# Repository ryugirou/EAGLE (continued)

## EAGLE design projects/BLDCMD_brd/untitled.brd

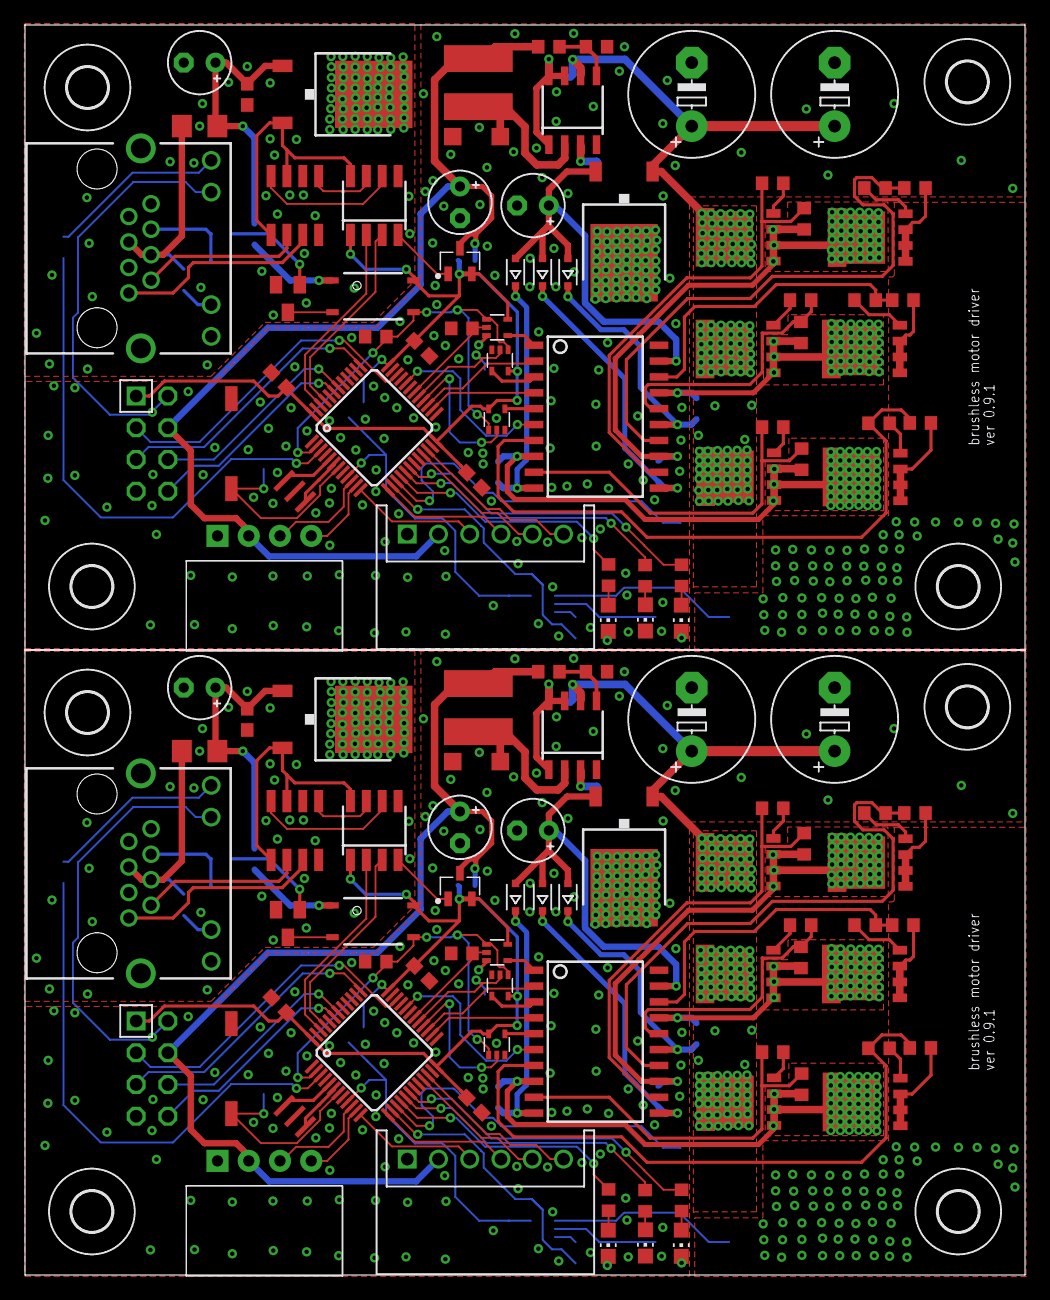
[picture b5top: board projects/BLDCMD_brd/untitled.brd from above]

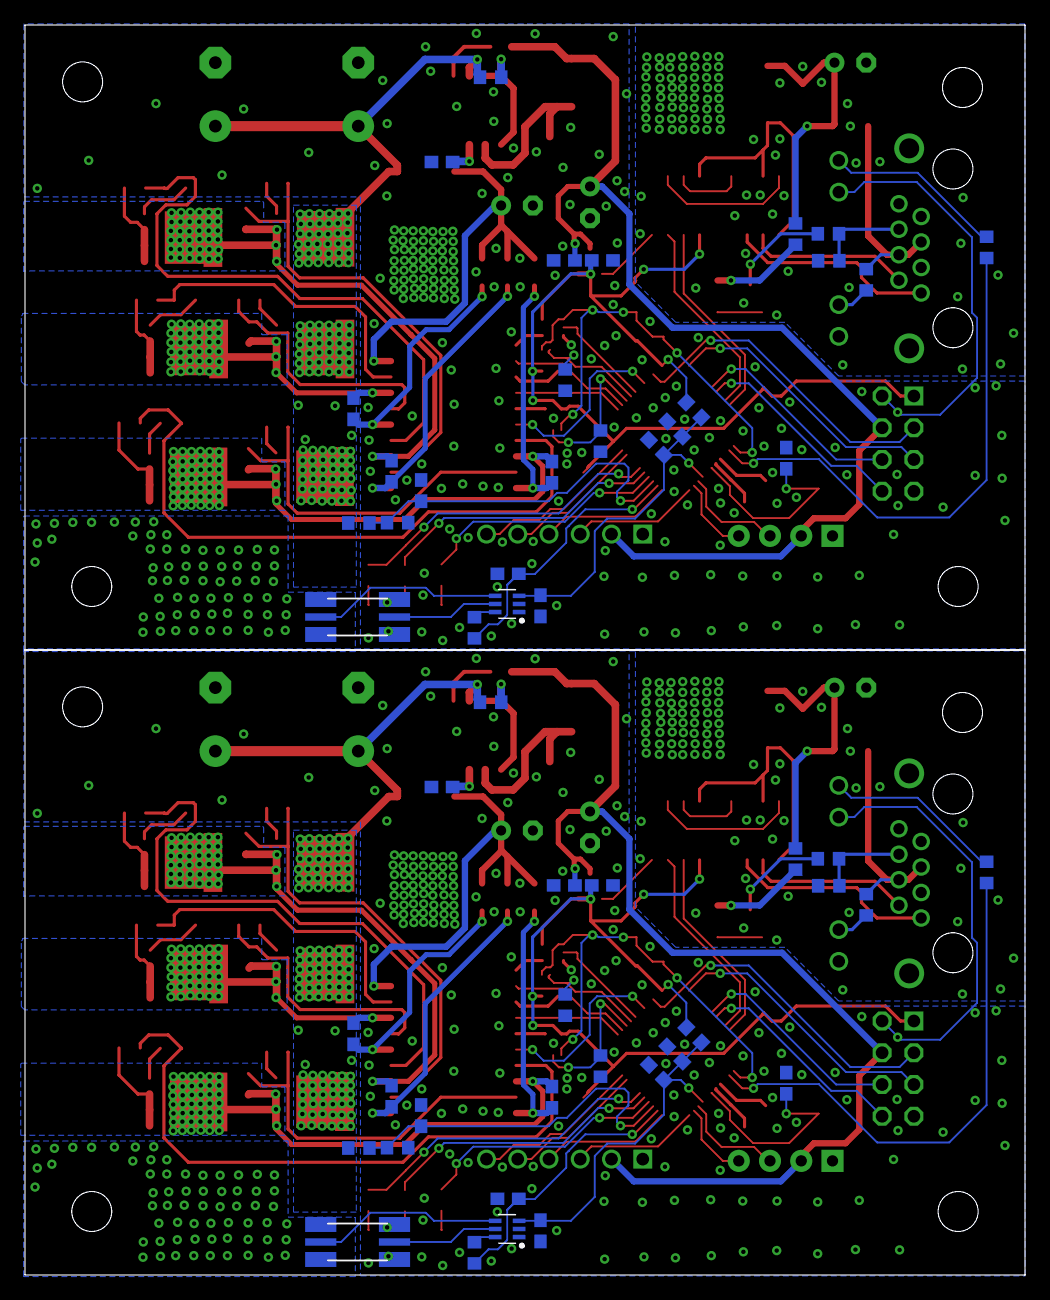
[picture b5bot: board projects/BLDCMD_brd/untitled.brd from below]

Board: 2 copper layers, 80.0 x 100.0 mm, 184 parts (52 on the bottom side), 160 nets.

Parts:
B1, B2: FERRITE_BEAD; R0603
C1, C2, C3, C8, C17, C18, C19, C22, C23, C24, C29, C38, C39, C40: C0603
C4, C5, C6, C7, C9, C12, C15, C25, C26, C27, C28, C30, C31, C36: 100n; C0603
C10, C14, C16, C34, C35, C37: E2,5-5
C11, C13, C32, C33: E5-10,5
C20, C41: 10u; C0603
C21, C42: 1u; C0603
CN1, CN2: S6B-XH-A
D1, D2, D3, D5, D6, D7: SOD323-R
D4, D8: SOD123
F1, F2: R1206
H1, H2, H3, H4, H5, H6, H7, H8: MOUNT-HOLE3.2; 3,2
IC1, IC11: STM32F103C8; LQFP48
IC2, IC13: SOIC20S
IC3, IC14: NCV7351D1E; SO08
IC4, IC5, IC6, IC20, IC21, IC22: 74AHCT1G08DCK; SC70-5
IC7, IC15: SI8621AB-B-IS; SO08
IC8, IC16: 7815DT; TO252
IC9, IC18: MC34063AD; SOIC8
IC10, IC17: 7805DT; TO252
IC12, IC19: BSS138BK; SOT23
L1, L2: L5852
LED1, LED2, LED3, LED4, LED5, LED6: CHIP-LED0805
Q1, Q2, Q3, Q4, Q5, Q6, Q7, Q8, Q9, Q10, Q11, Q12: N-MOSFET-; SOT669
R1, R2, R3, R4, R5, R6, R29, R30, R31, R32, R39, R40, R41, R42, R43, R60, R61, R62: 10; R0603
R7, R8, R9, R10, R11, R12, R33, R34, R35, R44, R45, R46: 10k; R0603
R13, R14, R15, R16, R17, R18, R22, R24, R36, R37, R38, R47, R48, R49, R53, R55: 1k; R0603
R19, R20, R21, R50, R51, R52: R0603
R23, R54: 100k; R0603
R25, R56: 1k?; R0603
R26, R57: 4k7; R0603
R27, R58: 470; R0603
R28, R59: CSS2H-2512
U$1, U$7: CSTCE8M00G55
U$2, U$9: TLP184; 11-4M1S
U$3, U$10: XH-4-SIDE; CON-XH-4-SIDE
U$4, U$11: SWITCH_TACTILETOP; SWITCH_TACTILE_3X6
U$5, U$14: NCS199; SOT65P210X110-6
U$6, U$12: XC6206; SOT95P240X110-3
U$8, U$13: MA04-2; MA04-2W
X1, X2: 8P8C-LED

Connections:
3V3A: B1.1, C18.1, C20.1, C21.1, IC1.9, U$5.3
3V3A1: B2.1, C39.1, C41.1, C42.1, IC11.9, U$14.3
5V_ISO: IC3.3, IC3.5, IC7.8, IC10.2
5V_ISO1: IC14.3, IC14.5, IC15.8, IC17.2
24V_ISO: C15.1, C16.+, F1.1, IC10.1, R25.2
24V_ISO1: C36.1, C37.+, F2.1, IC17.1, R56.2
!EMS: IC1.2, IC4.1, IC5.1, IC6.1, R24.2, U$2.3
!EMS1: IC11.2, IC20.1, IC21.1, IC22.1, R55.2, U$9.3
!RESET: C7.1, IC1.7, U$4.P$2
!RESET1: C28.1, IC11.7, U$11.P$2
+3V1: B2.2, C25.1, C26.1, C27.1, C31.1, IC11.24, IC11.36, IC11.48, IC15.1, IC20.5, IC21.5, IC22.5, U$9.4, U$12.2, U$13.8
+3V3: B1.2, C4.1, C5.1, C6.1, C12.1, IC1.24, IC1.36, IC1.48, IC4.5, IC5.5, IC6.5, IC7.1, U$2.4, U$6.2, U$8.8
+5V: C9.1, C14.+, CN1.2, L1.P$2, R19.2, U$3.P$2, U$6.3, U$8.5
+5V1: C30.1, C34.+, CN2.2, L2.P$2, R50.2, U$10.P$2, U$12.3, U$13.5
+15V: C10.+, D1.A, D2.A, D3.A, IC2.19, IC8.2
+15V1: C35.+, D5.A, D6.A, D7.A, IC13.19, IC16.2
CANRX: IC1.45, IC7.3
CANRX1: IC11.45, IC15.3
CANTX: IC1.46, IC7.2
CANTX1: IC11.46, IC15.2
ENC_A: IC1.10, U$3.P$3
ENC_A1: IC11.10, U$10.P$3
ENC_B: IC1.11, U$3.P$4
ENC_B1: IC11.11, U$10.P$4
GNDA: C4.2, C5.2, C6.2, C7.2, C8.2, C9.2, C10.-, C11.-, C12.2, C13.-, C14.-, C17.2, C18.2, C19.2, C20.2, C21.2, CN1.1, D4.A, IC1.8, IC1.23, IC1.35, IC1.44, IC1.47, IC2.20, IC4.3, IC5.3, IC6.3, IC7.4, IC8.3, IC9.4, LED1.C, LED2.C, LED3.C, R16.1, R17.1, R18.1, R20.1, R24.1, R28.1$1, R28.1$2, R31.1, U$1.2, U$3.P$1, U$4.P$1, U$5.1, U$5.2, U$6.1, U$8.2, U$8.7, X1.YC
GNDA1: C25.2, C26.2, C27.2, C28.2, C29.2, C30.2, C31.2, C32.-, C33.-, C34.-, C35.-, C38.2, C39.2, C40.2, C41.2, C42.2, CN2.1, D8.A, IC11.8, IC11.23, IC11.35, IC11.44, IC11.47, IC13.20, IC15.4, IC16.3, IC18.4, IC20.3, IC21.3, IC22.3, LED4.C, LED5.C, LED6.C, R47.1, R48.1, R49.1, R51.1, R55.1, R59.1$1, R59.1$2, R62.1, U$7.2, U$10.P$1, U$11.P$1, U$12.1, U$13.2, U$13.7, U$14.1, U$14.2, X2.YC
GNDIO: C15.2, C16.-, IC3.2, IC3.8, IC7.5, IC10.3, IC12.2, R23.1, X1.3, X1.7, X1.8, X1.GC, X1.M1, X1.M2
GNDIO1: C36.2, C37.-, IC14.2, IC14.8, IC15.5, IC17.3, IC19.2, R54.1, X2.3, X2.7, X2.8, X2.GC, X2.M1, X2.M2
HIN1: IC2.1, IC6.4
HIN2: IC2.3, IC5.4
HIN3: IC2.5, IC4.4
HIN4: IC13.5, IC20.4
HIN5: IC13.3, IC21.4
HIN6: IC13.1, IC22.4
HO1: IC2.12, R1.1, R7.1
HO2: IC2.16, R3.1, R9.1
HO3: IC2.9, R5.1, R11.1
HO4: IC13.12, R32.1, R44.1
HO5: IC13.16, R40.1, R46.1
HO6: IC13.9, R34.1, R42.1
IN_A: CN1.3, IC1.12
IN_A1: CN2.3, IC11.12
IN_B: CN1.4, IC1.13
IN_B1: CN2.4, IC11.13
IN_C: CN1.5, IC1.21
IN_C1: CN2.5, IC11.21
IN_D: CN1.6, IC1.22
IN_D1: CN2.6, IC11.22
ISENSE: C17.1, IC1.14, R29.2
ISENSE1: C38.1, IC11.14, R60.2
LED0: IC1.16, R13.1
LED1: IC1.17, R14.1
LED2: IC1.18, R15.1
LED3: IC11.16, R36.1
LED4: IC11.17, R37.1
LED5: IC11.18, R38.1
LED_CAN: IC1.3, R27.2
LED_CAN1: IC11.3, R58.2
LIN1: IC1.27, IC2.2
LIN2: IC1.26, IC2.4
LIN3: IC1.32, IC2.6
LIN4: IC11.27, IC13.2
LIN5: IC11.32, IC13.6
LIN6: IC11.26, IC13.4
LO1: IC2.14, R2.1, R8.1
LO2: IC2.18, R4.1, R10.1
LO3: IC2.7, R6.1, R12.1
LO4: IC13.14, R39.1, R45.1
LO5: IC13.18, R33.1, R41.1
LO6: IC13.7, R35.1, R43.1
unnamed: IC1.6, U$1.3
unnamed: IC1.5, U$1.1
unnamed: IC1.30, IC6.2, R18.2
unnamed: IC3.1, IC7.7
unnamed: IC1.28, IC4.2, R16.2
unnamed: C1.1, D1.C, IC2.15
unnamed: IC3.7, X1.1
unnamed: C2.1, D2.C, IC2.11
unnamed: C3.2, D3.C, IC2.10
unnamed: IC3.6, X1.2
unnamed: IC1.29, IC5.2, R17.2
unnamed: Q1.4, R1.2
unnamed: Q4.4, R2.2
unnamed: Q2.4, R3.2
unnamed: Q5.4, R4.2
unnamed: Q3.4, R5.2
unnamed: Q6.4, R6.2
unnamed: Q4.1, Q4.2, Q4.3, Q5.1, Q5.2, Q5.3, Q6.1, Q6.2, Q6.3, R8.2, R10.2, R12.2, R28.2$1, R28.2$2
unnamed: R28.2S, U$5.4
unnamed: R28.1S, U$5.5
unnamed: IC3.4, IC7.6
unnamed: R22.2, R23.2, X1.6
unnamed: LED3.A, R15.2
unnamed: LED1.A, R13.2
unnamed: LED2.A, R14.2
unnamed: F1.2, R26.2, X1.4, X1.5
unnamed: D4.C, IC9.2, L1.P$1
unnamed: IC9.5, R19.1, R20.2
unnamed: IC9.1, IC9.7, IC9.8, R21.1
unnamed: C8.1, IC9.3
unnamed: IC12.1, R22.1
unnamed: IC12.3, U$2.2
unnamed: R25.1, U$2.1
unnamed: IC11.6, U$7.3
unnamed: IC11.5, U$7.1
unnamed: R26.1, X1.GA
unnamed: R29.1, U$5.6
unnamed: R27.1, X1.YA
unnamed: IC11.28, IC20.2, R47.2
unnamed: LED6.A, R38.2
unnamed: LED4.A, R36.2
unnamed: LED5.A, R37.2
unnamed: Q7.4, R32.2
unnamed: Q10.4, R39.2
unnamed: Q8.4, R40.2
unnamed: Q11.4, R41.2
unnamed: Q9.4, R42.2
unnamed: Q12.4, R43.2
unnamed: C22.1, D5.C, IC13.15
unnamed: C23.1, D6.C, IC13.11
unnamed: C24.2, D7.C, IC13.10
unnamed: IC14.7, X2.1
unnamed: IC14.6, X2.2
unnamed: IC11.29, IC21.2, R48.2
unnamed: IC11.30, IC22.2, R49.2
unnamed: IC14.1, IC15.7
unnamed: IC14.4, IC15.6
unnamed: R53.2, R54.2, X2.6
unnamed: F2.2, R57.2, X2.4, X2.5
unnamed: D8.C, IC18.2, L2.P$1
unnamed: IC18.5, R50.1, R51.2
unnamed: IC18.1, IC18.7, IC18.8, R52.1
unnamed: C29.1, IC18.3
unnamed: IC19.1, R53.1
unnamed: IC19.3, U$9.2
unnamed: R56.1, U$9.1
unnamed: R57.1, X2.GA
unnamed: R58.1, X2.YA
unnamed: Q10.1, Q10.2, Q10.3, Q11.1, Q11.2, Q11.3, Q12.1, Q12.2, Q12.3, R33.2, R35.2, R45.2, R59.2$1, R59.2$2
unnamed: R59.2S, U$14.4
unnamed: R59.1S, U$14.5
unnamed: R60.1, U$14.6
SWCLK: IC1.37, U$8.4
SWCLK1: IC11.37, U$13.4
SWDIO: IC1.34, U$8.6
SWDIO1: IC11.34, U$13.6
U: C2.2, IC2.13, Q1.1, Q1.2, Q1.3, Q4.5, R7.2
U1: C23.2, IC13.13, Q7.1, Q7.2, Q7.3, Q10.5, R44.2
UART_RX: IC1.43, U$8.1
UART_RX1: IC11.43, U$13.1
UART_TX: IC1.42, U$8.3
UART_TX1: IC11.42, U$13.3
V: C1.2, IC2.17, Q2.1, Q2.2, Q2.3, Q5.5, R9.2
V1: C22.2, IC13.17, Q8.1, Q8.2, Q8.3, Q11.5, R46.2
VCC: C11.+, C13.+, IC8.1, IC9.6, Q1.5, Q2.5, Q3.5, R21.2, R30.2
VCC1: C32.+, C33.+, IC16.1, IC18.6, Q7.5, Q8.5, Q9.5, R52.2, R61.2
VSENSE: C19.1, IC1.15, R30.1, R31.2
VSENSE1: C40.1, IC11.15, R61.1, R62.2
W: C3.1, IC2.8, Q3.1, Q3.2, Q3.3, Q6.5, R11.2
W1: C24.1, IC13.8, Q9.1, Q9.2, Q9.3, Q12.5, R34.2

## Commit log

2019-06-26 almost finish schematic
2019-07-04 usbcan 修正済み BLDCMD完成
